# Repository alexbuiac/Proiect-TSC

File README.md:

# Proiect TSC 2025

## 1. Diagrama bloc a device-ului

```mermaid
flowchart TB
  USB-C -->|5V| Charger["Charger MCP73831"]
  Charger -->LiPo["Battery"]
  LiPo --> LDO["3V3 LDO"]
  
  ESP32["ESP32-C6-WROOM-1"]
  
  LDO -->|3.3V| ESP32
  LDO -->|3.3V| Display
  LDO -->|3.3V| SDCard
  LDO -->|3.3V| RTC
  LDO -->|3.3V| BME688
  LDO -->|3.3V| BatteryGauge
  
  ESP32 -- SPI --> Display["7.5 E-Ink Display Waveshare WSH-13187"]
  ESP32 -- SPI --> SDCard["SD Card Connector"]
  ESP32 -- GPIO --> Buttons["Buttons (3x)"]
  ESP32 -- I2C --> BME688["Environment Sensor BME688"]
  ESP32 -- I2C --> BatteryGauge["Battery Percentage Gauge MAX17048"]
  ESP32 -- I2C --> RTC["Clock DS3231"]
  ESP32 -- USB --> USB-C
  
  LDO -->|3.3V| ESP32
  LDO -->|3.3V| Display
  LDO -->|3.3V| SDCard
  LDO -->|3.3V| RTC
  LDO -->|3.3V| BME688
  LDO -->|3.3V| BatteryGauge
```
## 2. BIll of Materials

| Name of component | Device                                       | Check Prices                                                                                                | DataSheet                                                                                                 |
|-------------------|----------------------------------------------|-----------------------------------------------------------------------------------------------------------------|---------------------------------------------------------------------------------------------------------------|
| BOOT_BUTTON       | BUTTON_CUSYOMV1                             | https://industry.panasonic.com/global/en/products/control/switch/light-touch/number/evqpuj02k                  | https://industry.panasonic.com/global/en/products/control/switch/light-touch/number/evqpuj02k                  |
| C1                | ESP32_WROVER_EAGLE-LTSPICE_CC0402            | https://industry.panasonic.com/global/en/products/control/switch/light-touch/number/evqpuj02k                  | https://industry.panasonic.com/global/en/products/control/switch/light-touch/number/evqpuj02k                  |
| C1_BAT            | ESP32_WROVER_EAGLE-LTSPICE_CC0402            | #N/A                                                                                                            | #N/A                                                                                                           |
| C1_BAT1           | EAGLE-LTSPICE_CC0402                         | #N/A                                                                                                            | #N/A                                                                                                           |
| C1_BAT2           | EAGLE-LTSPICE_CC0402                         | #N/A                                                                                                            | #N/A                                                                                                           |
| C2                | ESP32_WROVER_EAGLE-LTSPICE_CC0402            | #N/A                                                                                                            | #N/A                                                                                                           |
| C2_BAT\           | ESP32_WROVER_EAGLE-LTSPICE_CC0402            | #N/A                                                                                                            | #N/A                                                                                                           |
| C3                | RCL_CPOL-EUCT3528                            | #N/A                                                                                                            | #N/A                                                                                                           |
| C4                | ESP32_WROVER_EAGLE-LTSPICE_CC0402            | #N/A                                                                                                            | #N/A                                                                                                           |
| C4_USB            | ESP32_WROVER_EAGLE-LTSPICE_CC0402            | #N/A                                                                                                            | #N/A                                                                                                           |
| C5                | ESP32_WROVER_EAGLE-LTSPICE_CC0402            | #N/A                                                                                                            | #N/A                                                                                                           |
| C5_USB            | ESP32_WROVER_EAGLE-LTSPICE_CC0402            | #N/A                                                                                                            | #N/A                                                                                                           |
| C6                | ESP32_WROVER_EAGLE-LTSPICE_CC0402            | #N/A                                                                                                            | #N/A                                                                                                           |
| C7                | ESP32_WROVER_EAGLE-LTSPICE_CC0402            | #N/A                                                                                                            | #N/A                                                                                                           |
| C8                | ESP32_WROVER_EAGLE-LTSPICE_CC0402            | #N/A                                                                                                            | #N/A                                                                                                           |
| C9                | EAGLE-LTSPICE_CC0402                         | #N/A                                                                                                            | #N/A                                                                                                           |
| C10               | ESP32_WROVER_EAGLE-LTSPICE_CC0402            | #N/A                                                                                                            | #N/A                                                                                                           |
| C10_SUPERCAP      | CPH3225A                                     | https://www.snapeda.com/parts/CPH3225A/Seiko+Instruments/view-part/?ref=eda                                   | https://www.snapeda.com/parts/CPH3225A/Seiko+Instruments/view-part/?ref=eda                                   |
| CHANGE_BUTTON     | BUTTON_CUSYOMV1                             | https://industry.panasonic.com/global/en/products/control/switch-light-touch/number/evqpuj02k                  | https://industry.panasonic.com/global/en/products/control/switch-light-touch/number/evqpuj02k                  |
| CHG_LED           | ADAFRUIT_LEDCHIP-LED0603                     | https://www.snapeda.com/parts/KP-1608SURCK/Kingbright/view-part/?ref=search&t=LED%200603                       | https://www.snapeda.com/parts/KP-1608SURCK/Kingbright/view-part/?ref=search&t=LED%200603                       |
| C_DELAY           | ESP32_WROVER_EAGLE-LTSPICE_CC0402            | #N/A                                                                                                            | #N/A                                                                                                           |
| D1                | USBLC6-2SC6Y                                 | https://www.snapeda.com/parts/USBLC6-2SC6Y/STMicroelectronics/view-part/?ref=eda                              | https://www.snapeda.com/parts/USBLC6-2SC6Y/STMicroelectronics/view-part/?ref=eda                              |
| D2                | ESP32_WROVER_AVX---SD0805S020S1R0_AVX_...    | https://eu.mouser.com/ProductDetail/KYOCERA-AVX/SD0805S020S1R0?qs=jCA%252BPfw4LHbpkAoSnwrdjw%3D%3D              | http://datasheets.avx.com/schottky.pdf                                                                         |
| D3                | MBR0530                                      | https://eu.mouser.com/ProductDetail/KYOCERA-AVX/SD0805S020S1R0?qs=jCA%252BPfw4LHbpkAoSnwrdjw%3D%3D              | https://eu.mouser.com/ProductDetail/KYOCERA-AVX/SD0805S020S1R0?qs=jCA%252BPfw4LHbpkAoSnwrdjw%3D%3D              |
| D4                | MBR0530                                      | https://www.snapeda.com/parts/MBR0530/Onsemi/view-part/?ref=eda                                                | https://www.snapeda.com/parts/MBR0530/Onsemi/view-part/?ref=eda                                                |
| D5                | MBR0530                                      | https://www.snapeda.com/parts/MBR0530/Onsemi/view-part/?ref=eda                                                | https://www.snapeda.com/parts/MBR0530/Onsemi/view-part/?ref=eda                                                |
| D6                | PGB1010603MR                                 | https://www.snapeda.com/parts/PGB1010603MR/Littelfuse/view-part/?ref=eda                                      | https://www.snapeda.com/parts/PGB1010603MR/Littelfuse/view-part/?ref=eda                                      |
| D7                | ESP32_WROVER_AVX---SD0805S020S1R0_AVX_...    | https://eu.mouser.com/ProductDetail/KYOCERA-AVX/SD0805S020S1R0?qs=jCA%252BPfw4LHbpkAoSnwrdjw%3D%3D              | http://datasheets.avx.com/schottky.pdf                                                                         |
| D8                | PGB1010603MR                                 | https://www.snapeda.com/parts/PGB1010603MR/Littelfuse/view-part/?ref=eda                                      | https://www.snapeda.com/parts/PGB1010603MR/Littelfuse/view-part/?ref=eda                                      |
| D9                | PGB1010603MR                                 | https://www.snapeda.com/parts/PGB1010603MR/Littelfuse/view-part/?ref=eda                                      | https://www.snapeda.com/parts/PGB1010603MR/Littelfuse/view-part/?ref=eda                                      |
| D10               | PGB1010603MR                                 | https://www.snapeda.com/parts/PGB1010603MR/Littelfuse/view-part/?ref=eda                                      | https://www.snapeda.com/parts/PGB1010603MR/Littelfuse/view-part/?ref=eda                                      |
| D11               | PGB1010603MR                                 | https://www.snapeda.com/parts/PGB1010603MR/Littelfuse/view-part/?ref=eda                                      | https://www.snapeda.com/parts/PGB1010603MR/Littelfuse/view-part/?ref=eda                                      |
| D12               | PGB1010603MR                                 | https://www.snapeda.com/parts/PGB1010603MR/Littelfuse/view-part/?ref=eda                                      | https://www.snapeda.com/parts/PGB1010603MR/Littelfuse/view-part/?ref=eda                                      |
| EPD_C1            | ESP32_WROVER_EAGLE-LTSPICE_CC0402            | #N/A                                                                                                            | #N/A                                                                                                           |
| EPD_C2            | ESP32_WROVER_EAGLE-LTSPICE_CC0402            | #N/A                                                                                                            | #N/A                                                                                                           |
| EPD_C5            | ESP32_WROVER_EAGLE-LTSPICE_CC0402            | #N/A                                                                                                            | #N/A                                                                                                           |
| EPD_C6            | ESP32_WROVER_EAGLE-LTSPICE_CC0402            | #N/A                                                                                                            | #N/A                                                                                                           |
| EPD_C7            | ESP32_WROVER_EAGLE-LTSPICE_CC0402            | #N/A                                                                                                            | #N/A                                                                                                           |
| EPD_C8            | ESP32_WROVER_EAGLE-LTSPICE_CC0402            | #N/A                                                                                                            | #N/A                                                                                                           |
| EPD_C9            | ESP32_WROVER_EAGLE-LTSPICE_CC0402            | #N/A                                                                                                            | #N/A                                                                                                           |
| EPD_C10           | ESP32_WROVER_EAGLE-LTSPICE_CC0402            | #N/A                                                                                                            | #N/A                                                                                                           |
| EPD_C11           | ESP32_WROVER_EAGLE-LTSPICE_CC0402            | #N/A                                                                                                            | #N/A                                                                                                           |
| EPD_C12           | ESP32_WROVER_EAGLE-LTSPICE_CC0402            | #N/A                                                                                                            | #N/A                                                                                                           |
| IC1               | BD5229G-TR                                   | https://componentsearchengine.com/part-view/BD5229G-TR/ROHM%20Semiconductor                                    | https://componentsearchengine.com/part-view/BD5229G-TR/ROHM%20Semiconductor                                    |
| IC4               | XC6220A331MR-G                               | https://componentsearchengine.com/part-view/XC6220A331MR-G/Torex                                              | https://componentsearchengine.com/part-view/XC6220A331MR-G/Torex                                              |
| J1                | FH34SRJ-24S-0.5SH_99_                        | https://componentsearchengine.com/part-view/XC6220A331MR-G/Torex                                              | https://componentsearchengine.com/part-view/XC6220A331MR-G/Torex                                              |
| J2                | SAMACSYS_PARTS_USB4110-GF-A                  | https://componentsearchengine.com/part-view/USB4110-GF-A/GCT%20(GLOBAL%20CONNECTOR%20TECHNOLOGY               | https://componentsearchengine.com/part-view/USB4110-GF-A/GCT%20(GLOBAL%20CONNECTOR%20TECHNOLOGY               |
| J3                | QWIIC_CONNECTORJS-1MM                        | #N/A                                                                                                            | #N/A                                                                                                           |
| J4                | 112A-TAAR-R03_ATTEND                         | https://store.comet.srl.ro/Catalogue/Product/43497/                                                            | https://store.comet.srl.ro/Catalogue/Product/43497/                                                            |
| L1                | 744043680IND_4828-WE-TPC_WRE                 | https://eu.mouser.com/ProductDetail/Wurth-Elektronik/744043680?qs=PGXP4M47uW6VkZq%252BkzjrHA%3D%3D               | https://eu.mouser.com/ProductDetail/Wurth-Elektronik/744043680?qs=PGXP4M47uW6VkZq%252BkzjrHA%3D%3D               |
| PFMF.050.1        | ESP32C6_VARISTORCN1812                       | https://www.mouser.co.uk/ProductDetail/EPCOS-TDK/B72520T0350K062?qs=dEfas%2FXlABIszF52uu7vrg%3D%3D              | https://www.mouser.co.uk/ProductDetail/EPCOS-TDK/B72520T0350K062?qs=dEfas%2FXlABIszF52uu7vrg%3D%3D              |
| Q1                | ESP32_WROVER_SPARKFUN-DISCRETESEMI_MOSFET_...| https://componentsearchengine.com/part-view/DMG2305UX-7/Diodes%20Incorporated                                  | https://componentsearchengine.com/part-view/DMG2305UX-7/Diodes%20Incorporated                                  |
| Q2                | ESP32_WROVER_SPARKFUN-DISCRETESEMI_MOSFET_...| #N/A                                                                                                            | #N/A                                                                                                           |
| Q3                | D8                                           | https://componentsearchengine.com/part-view/SI1308EDL-T1-GE3/Vishay                                           | https://componentsearchengine.com/part-view/SI1308EDL-T1-GE3/Vishay                                           |
| R1                | ESP32_WROVER_EAGLE-LTSPICE_RR0402            | #N/A                                                                                                            | #N/A                                                                                                           |
| R1-PINH           | ESP32_WROVER_EAGLE-LTSPICE_RR0402            | #N/A                                                                                                            | #N/A                                                                                                           |
| R1-PINH1          | ESP32_WROVER_EAGLE-LTSPICE_RR0402            | #N/A                                                                                                            | #N/A                                                                                                           |
| R1_BAT            | ESP32_WROVER_EAGLE-LTSPICE_RR0402            | #N/A                                                                                                            | #N/A                                                                                                           |
| R1_PWRUSB         | ESP32_WROVER_EAGLE-LTSPICE_RR0402            | #N/A                                                                                                            | #N/A                                                                                                           |
| R2                | ESP32_WROVER_EAGLE-LTSPICE_RR0402            | https://componentsearchengine.com/part-view/R0402%201%25%20100%20K%20(RC0402FR-07100KL                         | https://componentsearchengine.com/part-view/R0402%201%25%20100%20K%20(RC0402FR-07100KL                         |
| R2-PINH           | ESP32_WROVER_EAGLE-LTSPICE_RR0402            | #N/A                                                                                                            | #N/A                                                                                                           |
| R2-PINH1          | ESP32_WROVER_EAGLE-LTSPICE_RR0402            | #N/A                                                                                                            | #N/A                                                                                                           |
| R2-USB            | ESP32_WROVER_EAGLE-LTSPICE_RR0402            | #N/A                                                                                                            | #N/A                                                                                                           |
| R2-USB1           | ESP32_WROVER_EAGLE-LTSPICE_RR0402            | #N/A                                                                                                            | #N/A                                                                                                           |
| R2_BAT            | ESP32_WROVER_EAGLE-LTSPICE_RR0402            | #N/A                                                                                                            | #N/A                                                                                                           |
| R3                | ESP32_WROVER_EAGLE-LTSPICE_RR0402            | #N/A                                                                                                            | #N/A                                                                                                           |
| R4                | ESP32_WROVER_EAGLE-LTSPICE_RR0402            | #N/A                                                                                                            | #N/A                                                                                                           |
| R5                | ESP32_WROVER_EAGLE-LTSPICE_RR0402            | #N/A                                                                                                            | #N/A                                                                                                           |
| R6                | ESP32_WROVER_EAGLE-LTSPICE_RR0402            | #N/A                                                                                                            | #N/A                                                                                                           |
| R7                | ESP32_WROVER_EAGLE-LTSPICE_RR0402            | #N/A                                                                                                            | #N/A                                                                                                           |
| R8                | ESP32_WROVER_EAGLE-LTSPICE_RR0402            | #N/A                                                                                                            | #N/A                                                                                                           |
| R9                | ESP32_WROVER_EAGLE-LTSPICE_RR0402            | #N/A                                                                                                            | #N/A                                                                                                           |
| R10               | ESP32_WROVER_EAGLE-LTSPICE_RR0402            | #N/A                                                                                                            | #N/A                                                                                                           |
| RESET_BUTTON      | BUTTON_CUSYOMV1                             | https://industry.panasonic.com/global/en/products/control/switch/light-touch/number/evqpuj02k                  | https://industry.panasonic.com/global/en/products/control/switch/light-touch/number/evqpuj02k                  |
| R_BOOT            | ESP32_WROVER_EAGLE-LTSPICE_RR0402            | #N/A                                                                                                            | #N/A                                                                                                           |
| R_CAPACITOR       | ESP32_WROVER_EAGLE-LTSPICE_RR0402            | #N/A                                                                                                            | #N/A                                                                                                           |
| R_CHANGE          | ESP32_WROVER_EAGLE-LTSPICE_RR0402            | #N/A                                                                                                            | #N/A                                                                                                           |
| R_CL1             | ESP32_WROVER_EAGLE-LTSPICE_RR0402            | #N/A                                                                                                            | #N/A                                                                                                           |
| R_RESET           | ESP32_WROVER_EAGLE-LTSPICE_RR0402            | #N/A                                                                                                            | #N/A                                                                                                           |
| SENSOR2           | ESP32_WROVER_BME680_BME680                   | https://www.snapeda.com/parts/BME680/Bosch/view-part/?welcome=home                                            | https://www.snapeda.com/parts/BME680/Bosch/view-part/?welcome=home                                            |
| SJ1              | SJ                                           | https://grabcad.com/library/solder-jumpers-1                                                                   | https://grabcad.com/library/solder-jumpers-1                                                                   |
| TP1               | TPTP20R                                      | #N/A                                                                                                            | #N/A                                                                                                           |
| TP2               | TPTP20R                                      | #N/A                                                                                                            | #N/A                                                                                                           |
| TP3               | TPTP20R                                      | #N/A                                                                                                            | #N/A                                                                                                           |
| TP4               | TPTP20R                                      | #N/A                                                                                                            | #N/A                                                                                                           |
| TP5               | TPTP20R                                      | #N/A                                                                                                            | #N/A                                                                                                           |
| TP6               | TPTP20R                                      | #N/A                                                                                                            | #N/A                                                                                                           |
| TP7               | TPTP20R                                      | #N/A                                                                                                            | #N/A                                                                                                           |
| TP8               | TPTP20R                                      | #N/A                                                                                                            | #N/A                                                                                                           |
| TP9               | TPTP20R                                      | #N/A                                                                                                            | #N/A                                                                                                           |
| TP10              | TPTP20R                                      | #N/A                                                                                                            | #N/A                                                                                                           |
| TP11              | TPTP20R                                      | #N/A                                                                                                            | #N/A                                                                                                           |
| TP12              | TPTP20R                                      | #N/A                                                                                                            | #N/A                                                                                                           |
| TP13              | TPTP20R                                      | #N/A                                                                                                            | #N/A                                                                                                           |
| TP14              | TPTP20R                                      | #N/A                                                                                                            | #N/A                                                                                                           |
| TP15              | TPTP20R                                      | #N/A                                                                                                            | #N/A                                                                                                           |
| TP16              | TPTP20R                                      | #N/A                                                                                                            | #N/A                                                                                                           |
| TP17              | TPTP20R                                      | #N/A                                                                                                            | #N/A                                                                                                           |
| U1                | W25Q512JVEIQ                                 | https://www.snapeda.com/parts/W25Q512JVEIQ/Winbond+Electronics/view-part/?ref=eda                             | https://www.snapeda.com/parts/W25Q512JVEIQ/Winbond+Electronics/view-part/?ref=eda                             |
| U2                | ESP32-C6-WROOM-1-N8                          | https://www.snapeda.com/parts/ESP32-C6-WROOM-1-N8/Espressif+Systems/view-part/?ref=eda                        | https://www.snapeda.com/parts/ESP32-C6-WROOM-1-N8/Espressif+Systems/view-part/?ref=eda                        |
| U3                | DS3231SN#                                    | https://www.snapeda.com/parts/DS3231SN%23/Analog+Devices/view-part/?ref=eda                                   | https://www.snapeda.com/parts/DS3231SN%23/Analog+Devices/view-part/?ref=eda                                   |
| U4                | MAX17048G+T10                                | https://www.snapeda.com/parts/MAX17048G+T10/Analog+Devices/view-part/?ref=eda                                 | https://www.snapeda.com/parts/MAX17048G+T10/Analog+Devices/view-part/?ref=eda                                 |
| U5                | ESP32_WROVER_SPARKFUN-IC-POWER_MCP73831      | https://eu.mouser.com/ProductDetail/Microchip-Technology/MCP73831T-2ACI-OT?qs=yUQqVecv4qvbBQBGbHx0Mw%3D%3Dcf   | https://eu.mouser.com/ProductDetail/Microchip-Technology/MCP73831T-2ACI-OT?qs=yUQqVecv4qvbBQBGbHx0Mw%3D%3Dcf   |

## 3. Descrierea in detaliu a functionalitatilor hardware 

### 1. Microcontroller – ESP32-C6

- **Procesor**: 32-bit RISC-V, cu frecvență de până la 160MHz.
    
- **Memorie**: 512KB SRAM intern și 8MB flash extern (W25Q512JVEIQ).
    
- **Conectivitate**: Wi-Fi 6 (802.11ax), Bluetooth 5 (LE), USB 2.0 (full-speed).
    
- **Periferice**: SPI, I²C, UART, GPIO multiple.
    
- **Consum**: Posibilitate de moduri low-power (sleep, deep sleep).

### 2. Senzor de Mediu – BME688

- **Parametri măsurați**: Temperatură, Umiditate, Presiune și Calitate aer (VOC/eCO2).
    
- **Interfață**: I²C la 400kHz (SDA și SCL).
    
- **Consum**: Foarte mic (în jur de 2.1µA în standby și până la câteva mA în mod de măsurare).

### 3. Afișajul E-Paper (7.5 inch)

- **Model**: Waveshare (sau echivalent) cu rezoluție 800×480.
    
- **Interfață**: 4-wire SPI + semnale de control (CS, DC, RST, BUSY).
    
- **Consum**: Foarte redus în mod static (după refresh), dar necesită un curent mai mare în timpul refresh-ului (aprox. 15–25mA, în funcție de modul de actualizare).

### 4. Baterie și Managementul Energiei

- **Baterie Li-Po 2500mAh** (3.7V nominal).
    
- **IC de Încărcare**: MCP73831 (Microchip) – încărcare Li-Po prin USB-C (până la 1A).
    
- **Fuel Gauge**: MAX17048 – monitorizează nivelul de încărcare, tensiunea și starea bateriei (I²C).
    
- **LDO**: XC6220A331MR-G (exemplu) sau echivalent, pentru a asigura 3.3V stabil pentru microcontroller și restul componentelor.

### 5. USB-C Port

- **Rol**: Încărcare baterie + Transfer de date (USB 2.0 full-speed).
    
- **Protecții**: ESD (USBLC6-2SC6Y) + rezistențe de terminare.
    
- **Posibilitate**: Actualizări firmware prin USB (bootloader + tool extern) sau direct OTA prin Wi-Fi.

### 6. Butoane (3x Tactile Switch)

- **Tip**: Tactile switch Panasonic (sau echivalent).
    
- **Funcții**: Navigare meniu, selectare opțiune, întoarcere pagină etc.
    
- **Conexiune**: Fiecare buton se leagă la un GPIO al ESP32-C6 printr-un circuit de debouncing (rezistență și condensator) sau se poate face debouncing în firmware.

### 7. Conector Qwiic (I²C)

- Conector standard cu 4 pini: VCC, GND, SDA, SCL.
    
- Permite atașarea rapidă a altor senzori sau module I²C (expansiune, testare, prototipare rapidă).

### 8. SD Memory Card Connector (112A-TAAR-R03)

- **Rol**: Posibilitate de stocare externă pentru e-book-uri, log-uri sau update-uri firmware.
    
- **Interfață**: Poate fi SD (1-bit / 4-bit) sau SPI, în funcție de configurația firmware-ului.

### 10. Memorii Suplimentare

- **W25Q512JVEIQ** (Flash extern) – conectat la ESP32-C6 prin SPI dedicat (quad SPI).
    
    - Aici se stochează firmware-ul și datele mari (e-book-uri etc.).

### 9. RTC – DS3231

- **Funcție**: Asigură un ceas de timp real foarte precis.
    
- **Interfață**: I²C (aceeași magistrală cu BME688 și MAX17048).
    
- **Backup**: Supercondensator sau baterie secundară pentru a menține timpul și în absența alimentării principale.    

## 4. Folosirea pinilor ESP32-C6

| Pin ESP32-C6    | Componentă / Semnal                       | De ce?                                                        |
| --------------- | ----------------------------------------- | ------------------------------------------------------------- |
| **GPIO1 (SDA)** | I²C SDA (BME688, MAX17048, DS3231, Qwiic) | Partajare magistrală I²C pentru toți senzorii și RTC.         |
| **GPIO2 (SCL)** | I²C SCL (BME688, MAX17048, DS3231, Qwiic) | Linia de clock pentru I²C.                                    |
| **GPIO5**       | SPI MISO (E-Paper)                        | Citirea datelor/statusului display-ului (dacă e suportat).    |
| **GPIO6**       | SPI MOSI (E-Paper)                        | Trimiterea datelor către e-paper.                             |
| **GPIO7**       | SPI CLK (E-Paper)                         | Semnal de clock pentru e-paper.                               |
| **GPIO8**       | SPI CS (E-Paper)                          | Chip Select pentru e-paper.                                   |
| **GPIO9**       | E-Paper DC (Data/Command)                 | Semnal care diferențiază datele de comenzile pentru afișaj.   |
| **GPIO10**      | E-Paper RST                               | Reset hardware pentru e-paper.                                |
| **GPIO11**      | E-Paper BUSY                              | Intrare din display, indică dacă este ocupat.                 |
| **GPIO12**      | Button #1                                 | Intrare digitală pentru buton (ex. NEXT page).                |
| **GPIO13**      | Button #2                                 | Intrare digitală pentru buton (ex. PREV page).                |
| **GPIO14**      | Button #3                                 | Intrare digitală pentru buton (ex. MENU/OK).                  |
| **GPIO15**      | MAX17048 ALERT (opțional)                 | Avertizare nivel baterie scăzut.                              |
| **GPIO16**      | USB D+ (intern la USB PHY)                | Pin dedicat pentru USB 2.0. (În mod normal pin hardware fix). |
| **GPIO17**      | USB D- (intern la USB PHY)                | Pin dedicat pentru USB 2.0. (La fel, pin fix).                |
| **GPIO18**      | LED de status (opțional)                  | Indicator pentru diverse stări (Wi-Fi, încărcare, etc.).      |
| **GPIO19**      | SD Card CS (opțional)                     | Chip Select pentru cardul SD (dacă se folosește SPI).         |
| **GPIO20**      | SD Card MISO (opțional)                   | Intrare date de la card SD.                                   |
| **GPIO21**      | SD Card MOSI (opțional)                   | Ieșire date către card SD.                                    |
| **GPIO4**       | SD Card CLK (opțional)                    | Semnal de clock pentru card SD (SPI).                         |

## 5. Imagini

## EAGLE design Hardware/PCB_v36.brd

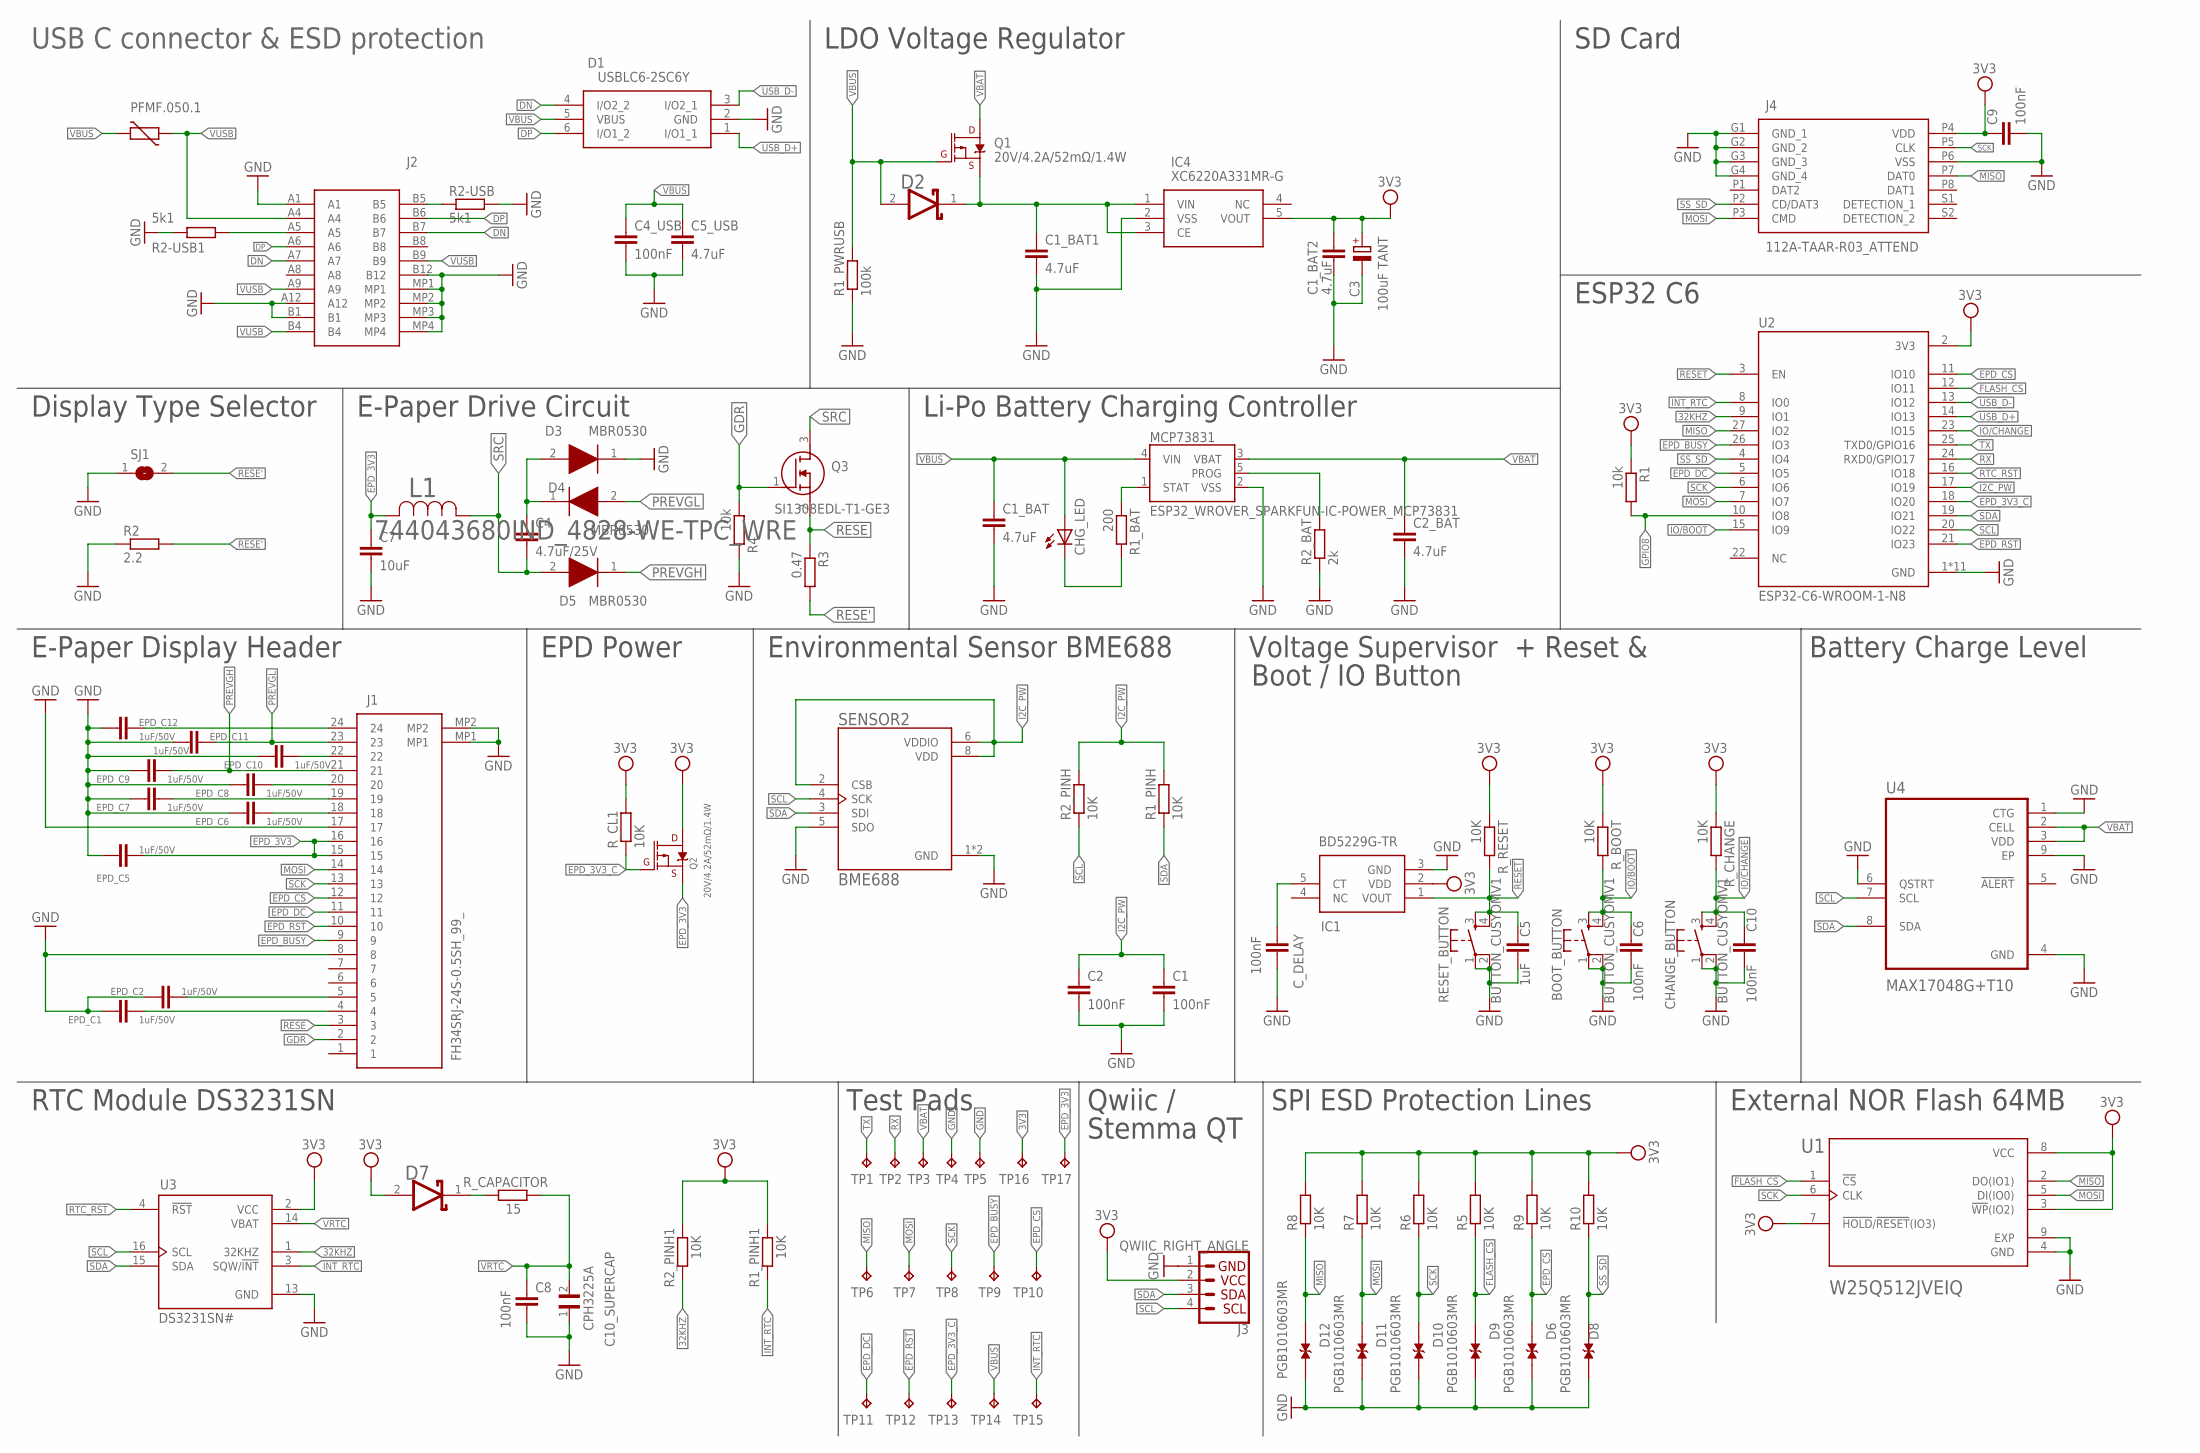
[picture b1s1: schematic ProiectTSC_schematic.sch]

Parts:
BOOT_BUTTON: BUTTON_CUSYOMV1; MYBUTTON
C1, C2, C4_USB, C6, C8, C9, C10: 100nF; ESP32_WROVER_EAGLE-LTSPICE_C0402
C1_BAT, C1_BAT1, C1_BAT2, C2_BAT, C5_USB: 4.7uF; ESP32_WROVER_EAGLE-LTSPICE_C0402
C3: 100uF TANT; RCL_CT3528
C4: 4.7uF/25V; ESP32_WROVER_EAGLE-LTSPICE_C0402
C5: 1uF; ESP32_WROVER_EAGLE-LTSPICE_C0402
C7: 10uF; ESP32_WROVER_EAGLE-LTSPICE_C0402
C10_SUPERCAP: CPH3225A; CAPCP3225X100N
CHANGE_BUTTON: BUTTON_CUSYOMV1; MYBUTTON
CHG_LED: ADAFRUIT_LEDCHIP-LED0603; ADAFRUIT_CHIP-LED0603
C_DELAY: 100nF; ESP32_WROVER_EAGLE-LTSPICE_C0402
D1: USBLC6-2SC6Y; SOT95P280X145-6N
D2, D7: SD0805S020S1R0; ESP32_WROVER_AVX---SD0805S020S1R0_AVX_SD0805S020S1R0_0
D3, D4, D5: MBR0530; SOD3716X135N
D6, D8, D9, D10, D11, D12: PGB1010603MR; DIOC1608X36N
EPD_C1, EPD_C2, EPD_C5, EPD_C6, EPD_C7, EPD_C8, EPD_C9, EPD_C10, EPD_C11, EPD_C12: 1uF/50V; ESP32_WROVER_EAGLE-LTSPICE_C0402
IC1: BD5229G-TR; SOT95P280X120-5N
IC4: XC6220A331MR-G; SOT95P280X120-5N
J1: FH34SRJ-24S-0.5SH_99_; FH34SRJ24S05SH99
J2: SAMACSYS_PARTS_USB4110-GF-A; SAMACSYS_PARTS_USB4110GFA
J3: QWIIC_RIGHT_ANGLE; JST04_1MM_RA
J4: 112A-TAAR-R03_ATTEND; 112ATAARR03ATTEND
L1: 744043680IND_4828-WE-TPC_WRE; IND_4828-WE-TPC_WRE
MCP73831: ESP32_WROVER_SPARKFUN-IC-POWER_MCP73831; ESP32_WROVER_SPARKFUN-IC-POWER_SOT23-5
PFMF.050.1: ESP32C6_VARISTORCN1812; ESP32C6_VARISTOR_CT/CN1812
Q1, Q2: 20V/4.2A/52mΩ/1.4W; ESP32_WROVER_SPARKFUN-DISCRETESEMI_SOT23-3
Q3: SI1308EDL-T1-GE3; SOT65P210X110-3N
R1, R4: 10k; ESP32_WROVER_EAGLE-LTSPICE_R0402
R1_BAT: 200; ESP32_WROVER_EAGLE-LTSPICE_R0402
R1_PINH, R1_PINH1, R2_PINH, R2_PINH1, R5, R6, R7, R8, R9, R10: 10K; ESP32_WROVER_EAGLE-LTSPICE_R0402
R1_PWRUSB: 100k; ESP32_WROVER_EAGLE-LTSPICE_R0402
R2: 2.2; ESP32_WROVER_EAGLE-LTSPICE_R0402
R2-USB, R2-USB1: 5k1; ESP32_WROVER_EAGLE-LTSPICE_R0402
R2_BAT: 2k; ESP32_WROVER_EAGLE-LTSPICE_R0402
R3: 0.47; ESP32_WROVER_EAGLE-LTSPICE_R0402
RESET_BUTTON: BUTTON_CUSYOMV1; MYBUTTON
R_BOOT: 10K; ESP32_WROVER_EAGLE-LTSPICE_R0402
R_CAPACITOR: 15; ESP32_WROVER_EAGLE-LTSPICE_R0402
R_CHANGE: 10K; ESP32_WROVER_EAGLE-LTSPICE_R0402
R_CL1: 10K; ESP32_WROVER_EAGLE-LTSPICE_R0402
R_RESET: 10K; ESP32_WROVER_EAGLE-LTSPICE_R0402
SENSOR2: BME688; ESP32_WROVER_BME680_PSON80P300X300X100-8N
SJ1: SJ
TP1, TP2, TP3, TP4, TP5, TP6, TP7, TP8, TP9, TP10, TP11, TP12, TP13, TP14, TP15, TP16, TP17: TPTP20R; TP20R
U1: W25Q512JVEIQ; SON127P600X800X80-9N
U2: ESP32-C6-WROOM-1-N8; XCVR_ESP32-C6-WROOM-1-N8
U3: DS3231SN#; SOIC127P1032X265-16N
U4: MAX17048G+T10; SON50P200X200X80-9N

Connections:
3V3: C1_BAT2.1, C3.+, C9.1, D7.2 (ANODE), IC1.2 (VDD), IC4.5 (VOUT), J3.2, J4.P4 (VDD), Q2.3 (D), R1.1, R1_PINH1.2, R2_PINH1.2, R5.2, R6.2, R7.2, R8.2, R9.2, R10.2, R_BOOT.1, R_CHANGE.1, R_CL1.2, R_RESET.1, TP16.TP, U1.3 (!WP!(IO2)), U1.7 (!HOLD!/!RESET!(IO3)), U1.8 (VCC), U2.2 (3V3), U3.2 (VCC)
32KHZ: R2_PINH1.1, U2.9 (IO1), U3.1 (32KHZ)
DN: D1.4 (I/O2_2), J2.A7, J2.B7
DP: D1.6 (I/O1_2), J2.A6, J2.B6
EPD_3V3: C7.1, EPD_C5.1, J1.15, J1.16, L1.2, Q2.2 (S), TP17.TP
EPD_3V3_C: Q2.1 (G), R_CL1.1, TP13.TP, U2.18 (IO20)
EPD_BUSY: J1.9, TP9.TP, U2.26 (IO3)
EPD_CS: D6.1, J1.12, R9.1, TP10.TP, U2.11 (IO10)
EPD_DC: J1.11, TP11.TP, U2.5 (IO5)
EPD_RST: J1.10, TP12.TP, U2.21 (IO23)
FLASH_CS: D9.1, R5.1, U1.1 (!CS), U2.12 (IO11)
GDR: J1.2, Q3.1 (G), R4.1
GND: BOOT_BUTTON.1, BOOT_BUTTON.2, C1.2, C1_BAT.2, C1_BAT1.2, C1_BAT2.2, C2.2, C2_BAT.2, C3.-, C4_USB.2, C5.2, C5_USB.2, C6.2, C7.2, C8.2, C9.2, C10.2, C10_SUPERCAP.1, CHANGE_BUTTON.1, CHANGE_BUTTON.2, C_DELAY.2, D1.2 (GND), D3.1 (K), D6.2, D8.2, D9.2, D10.2, D11.2, D12.2, EPD_C1.2, EPD_C2.2, EPD_C5.2, EPD_C6.2, EPD_C7.2, EPD_C8.2, EPD_C9.2, EPD_C10.2, EPD_C11.2, EPD_C12.2, IC1.3 (GND), IC4.2 (VSS), J1.8, J1.17, J1.MP1, J1.MP2, J2.A1, J2.A12, J2.B1, J2.B12, J2.MP1, J2.MP2, J2.MP3, J2.MP4, J3.1, J4.G1 (GND_1), J4.G2 (GND_2), J4.G3 (GND_3), J4.G4 (GND_4), J4.P6 (VSS), MCP73831.2 (VSS), R1_PWRUSB.1, R2.1, R2-USB.2, R2-USB1.1, R2_BAT.1, R4.2, RESET_BUTTON.1, RESET_BUTTON.2, SENSOR2.1 (GND), SENSOR2.5 (SDO), SENSOR2.7 (GND), SJ1.1, TP4.TP, TP5.TP, U1.4 (GND), U1.9 (EXP), U2.1 (GND), U2.28 (GND), U2.29_1 (GND), U2.29_2 (GND), U2.29_3 (GND), U2.29_4 (GND), U2.29_5 (GND), U2.29_6 (GND), U2.29_7 (GND), U2.29_8 (GND), U2.29_9 (GND), U3.13 (GND), U4.1 (CTG), U4.4 (GND), U4.6 (QSTRT), U4.9 (EP)
GPIO8: R1.2, U2.10 (IO8)
I2C_PW: C1.1, C2.1, R1_PINH.2, R2_PINH.2, SENSOR2.2 (CSB), SENSOR2.6 (VDDIO), SENSOR2.8 (VDD), U2.17 (IO19)
INT_RTC: R1_PINH1.1, TP15.TP, U2.8 (IO0), U3.3 (SQW/!INT)
IO/BOOT: BOOT_BUTTON.3, BOOT_BUTTON.4, C6.1, R_BOOT.2, U2.15 (IO9)
IO/CHANGE: C10.1, CHANGE_BUTTON.3, CHANGE_BUTTON.4, R_CHANGE.2, U2.23 (IO15)
MISO: D12.1, J4.P7 (DAT0), R8.1, TP6.TP, U1.2 (DO(IO1)), U2.27 (IO2)
MOSI: D11.1, J1.14, J4.P3 (CMD), R7.1, TP7.TP, U1.5 (DI(IO0)), U2.7 (IO7)
unnamed: J2.A5, R2-USB1.2
unnamed: C4.1, D3.2 (A), D4.1 (K)
unnamed: MCP73831.1 (STAT), R1_BAT.1
unnamed: CHG_LED.C, R1_BAT.2
unnamed: J2.B5, R2-USB.1
unnamed: MCP73831.5 (PROG), R2_BAT.2
unnamed: EPD_C10.1, J1.22
unnamed: EPD_C12.1, J1.24
unnamed: C1_BAT1.1, D2.1 (CATHODE), IC4.1 (VIN), IC4.3 (CE), Q1.2 (S)
unnamed: EPD_C8.1, J1.20
unnamed: EPD_C7.1, J1.19
unnamed: EPD_C6.1, J1.18
unnamed: EPD_C2.1, J1.5
unnamed: EPD_C1.1, J1.4
unnamed: C_DELAY.1, IC1.5 (CT)
unnamed: D7.1 (CATHODE), R_CAPACITOR.1
PREVGH: D5.1 (K), EPD_C9.1, J1.21
PREVGL: D4.2 (A), EPD_C11.1, J1.23
RESE: J1.3, Q3.2 (S), R3.1
RESE': R2.2, R3.2, SJ1.2
RESET: C5.1, IC1.1 (VOUT), RESET_BUTTON.3, RESET_BUTTON.4, R_RESET.2, U2.3 (EN)
RTC_RST: U2.16 (IO18), U3.4 (!RST)
RX: TP2.TP, U2.24 (RXD0/GPIO17)
SCK: D10.1, J1.13, J4.P5 (CLK), R6.1, TP8.TP, U1.6 (CLK), U2.6 (IO6)
SCL: J3.4, R2_PINH.1, SENSOR2.4 (SCK), U2.20 (IO22), U3.16 (SCL), U4.7 (SCL)
SDA: J3.3, R1_PINH.1, SENSOR2.3 (SDI), U2.19 (IO21), U3.15 (SDA), U4.8 (SDA)
SRC: C4.2, D5.2 (A), L1.1, Q3.3 (D)
SS_SD: D8.1, J4.P2 (CD/DAT3), R10.1, U2.4 (IO4)
TX: TP1.TP, U2.25 (TXD0/GPIO16)
USB_D+: D1.1 (I/O1_1), U2.14 (IO13)
USB_D-: D1.3 (I/O2_1), U2.13 (IO12)
VBAT: C2_BAT.1, MCP73831.3 (VBAT), Q1.3 (D), TP3.TP, U4.2 (CELL), U4.3 (VDD)
VBUS: C1_BAT.1, C4_USB.1, C5_USB.1, CHG_LED.A, D1.5 (VBUS), D2.2 (ANODE), MCP73831.4 (VIN), PFMF.050.1.2, Q1.1 (G), R1_PWRUSB.2, TP14.TP
VRTC: C8.1, C10_SUPERCAP.2, R_CAPACITOR.2, U3.14 (VBAT)
VUSB: J2.A4, J2.A9, J2.B4, J2.B9, PFMF.050.1.1

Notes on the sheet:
USB C connector & ESD protection
LDO Voltage Regulator
SD Card
ESP32 C6
Display Type Selector
E-Paper Drive Circuit
Li-Po Battery Charging Controller
E-Paper Display Header
EPD Power
Environmental Sensor BME688
Voltage Supervisor + Reset &
Boot / IO Button
Battery Charge Level
RTC Module DS3231SN
Test Pads
Qwiic /
Stemma QT
SPI ESD Protection Lines
External NOR Flash 64MB

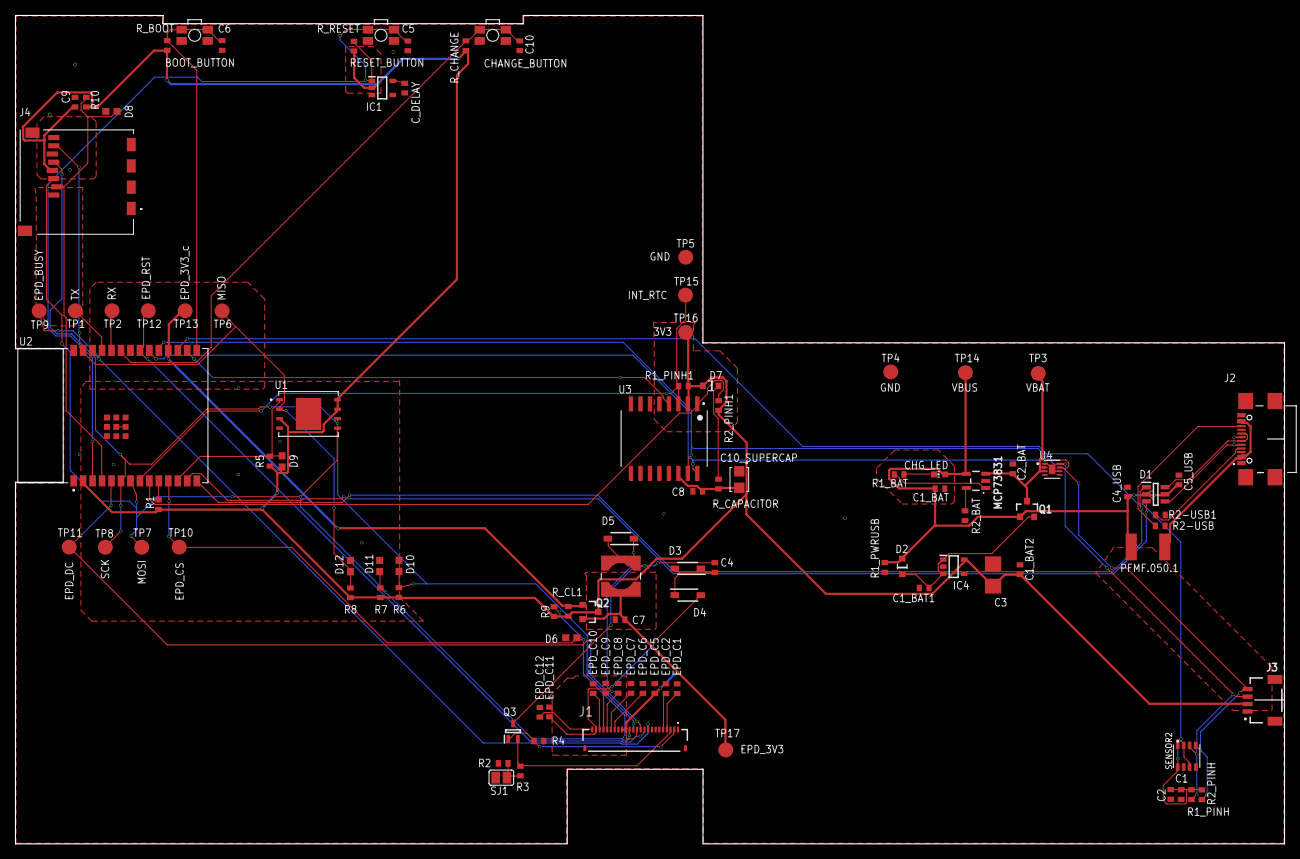
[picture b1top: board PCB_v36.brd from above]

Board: 2 copper layers, 170.2 x 111.1 mm, 103 parts (0 on the bottom side), 55 nets.

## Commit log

2025-04-06 readme
2025-04-06 license
2025-04-06 asdaw
2025-04-06 asdawd
2025-04-16 Create dummy

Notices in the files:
parts and their libraries:
COPYRIGHT: Copyright (C) 2024 Ultra Librarian. All rights reserved.
